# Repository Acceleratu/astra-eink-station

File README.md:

# A solar e-paper weather station

A build journal and prototype design by Acceleratu. Read the [English article](index.html) or the [Romanian article](ro.html). Both articles work directly from disk. The HTTP preview opens Markdown documents in the selected language. For the compact hardware download, open [station-project.zip](station-project.zip).

The design uses an nRF54L15 module, a 4.2-inch Waveshare e-paper panel, BME280, solar harvesting and USB-C charging. The hardware has been checked in software. Power-up, battery charging, radio range, USB plug fit and the fit of the printed enclosure still need to be tested on a prototype.

## Inside the project download

- Open `schematic/astra.sch`, `board/astra.brd` and `hardware/astra.lbr` as editable Autodesk Electronics / EAGLE sources. The PDF and assembly drawing are also included.
- `fab/` contains the manufacturing layers, drills, IPC netlist, BOM, placements, stencil geometry and test pad map. The catalog availability snapshot records the design date.
- `mechanical/` contains the populated board and assembled case in STEP, the enclosure generator, 11 printable STL files, drawings for the cut parts and the illustrated assembly guide. STEP preserves the assembly geometry. The CAD generator supplies editable dimensions and construction logic.
- `firmware/` contains the Zephyr source, host-side tests and the compiled Intel HEX. See its README for the pinned build environment.
- `docs/`, `verification/` and the project journal record engineering decisions, digital tests, exceptions and outstanding physical tests.

## Reading the evidence

The article uses the original test reports. SHA-256 values inside historical reports identify the files used for those runs. The distributed STEP headers, image/PDF metadata, drawing metadata, STL headers and Gerber export comments have been cleaned. STEP geometry and STL triangles are preserved. The USB inspection comparator uses the distributed assembly's checksum. Use the root `SHA256SUMS` to verify the download and the distributed files.

The archives contain the selected engineering deliverables. Third-party toolchains, vendor part libraries, cloud project archives, raw agent sessions and machine-specific build products are excluded. The usage table contains aggregate counts for the three hardware requests.

## Interactive explorer

Both articles include the same local viewer. Use it over HTTP. The seven schematic sheets have selectable reference designators and net labels. The PCB view combines the ten manufacturing plots with five CAD overlays. It includes a distance ruler in millimetres and component and net lookup. The 3D board includes 139 fitted components. The enclosure adds 111 named meshes and an exploded assembly, section cut and USB close-up. Rendered meshes are for inspection. The STEP assemblies and Gerber/drill exports remain the engineering files.

Open `?view=case&pose=spread#explorer` for the exploded assembly or `?view=pcb3&part=J101#explorer` for the USB connector. Use drag and pinch on touchscreens, or focus the viewport and use the arrow keys, +, − and 0. The viewer serves its own assets and Three.js. To rebuild the JavaScript, run `npm install` and `npm run build` in `explorer/`. The generator in `explorer/tools/drawings.py` takes the vector schematic PDF as its input. The public PDF is flattened. The mesh converter takes the original CAD presentation mesh manifest and the populated PCB STEP.

### Fusion workspace

The explorer opens with Fusion Electronics colours. All seven native schematic exports are registered to the interactive labels. Both standard PCB faces use the original Fusion exports. Custom layer combinations use the 37 individually exported design layers, registered on the board outline. The vector PDF and manufacturing plot views are available in the display selector.

The 3D canvas uses the saved Fusion orthographic cameras, the shaded assembly, a selectable orientation cube, grid, component browser and optional visible edges. The finished board uses meshes from the native 3D PCB, including the package bodies, plated holes, exposed lands and solder mask. Surface colours come from Fusion captures. Each projected sample is matched to the visible body and its depth. The component cameras cover the USB-C and FPC connectors, radio module, solar harvester, sensor and button. The original screenshots are available for direct comparison at full resolution. Their pixels are preserved losslessly. Browser rendering in freely chosen orientations uses WebGL.

Use `?workspace=1&view=case&camera=05-usb#explorer` to open the USB inspection camera in the full-window workspace. The local release contains all the data used by these views.

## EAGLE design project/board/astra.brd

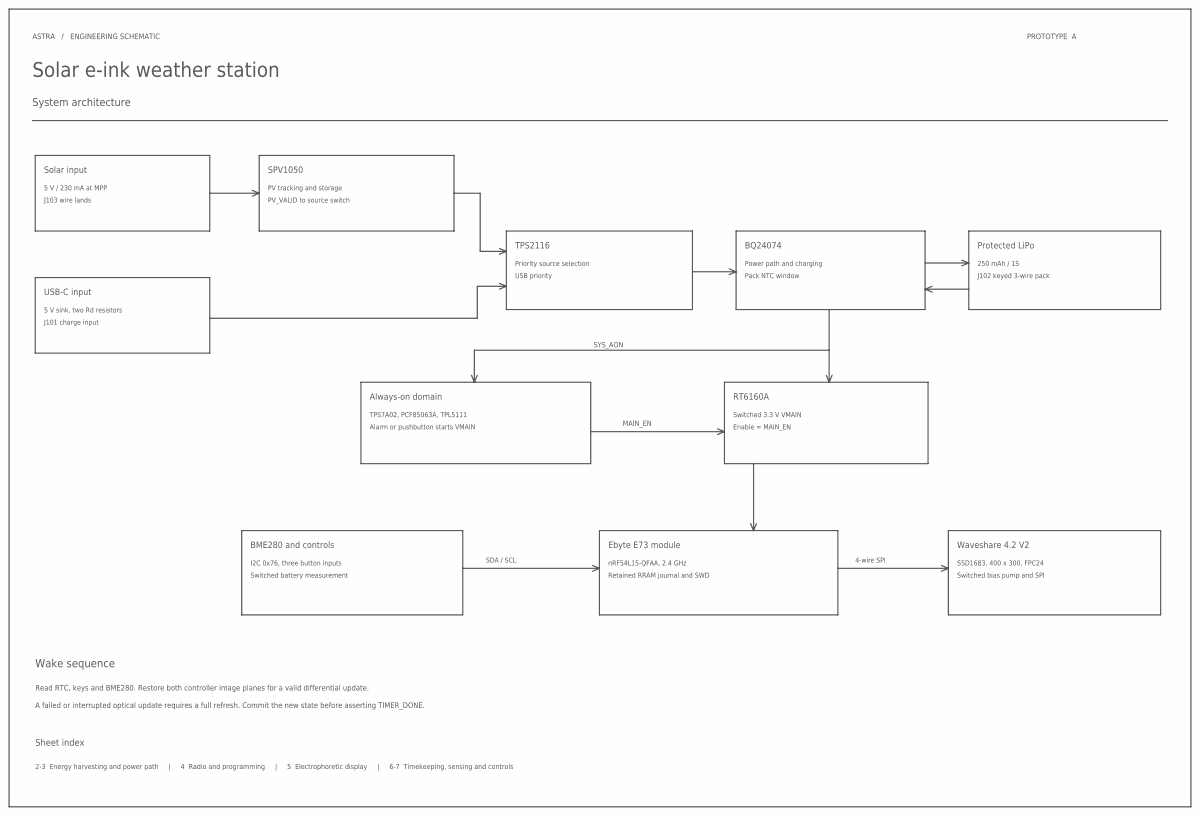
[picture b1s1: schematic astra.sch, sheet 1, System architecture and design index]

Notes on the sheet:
ASTRA / ENGINEERING SCHEMATIC
Solar e-ink weather station
System architecture
PROTOTYPE A
Solar input
5 V / 230 mA at MPP
J103 wire lands
USB-C input
5 V sink, two Rd resistors
J101 charge input
SPV1050
PV tracking and storage
PV_VALID to source switch
TPS2116
Priority source selection
USB priority
BQ24074
Power path and charging
Pack NTC window
Protected LiPo
250 mAh / 1S
J102 keyed 3-wire pack
RT6160A
Switched 3.3 V VMAIN
Enable = MAIN_EN
Always-on domain
TPS7A02, PCF85063A, TPL5111
Alarm or pushbutton starts VMAIN
SYS_AON
MAIN_EN
BME280 and controls
I2C 0x76, three button inputs
Switched battery measurement
Ebyte E73 module
nRF54L15-QFAA, 2.4 GHz
Retained RRAM journal and SWD
Waveshare 4.2 V2
SSD1683, 400 x 300, FPC24
Switched bias pump and SPI
SDA / SCL

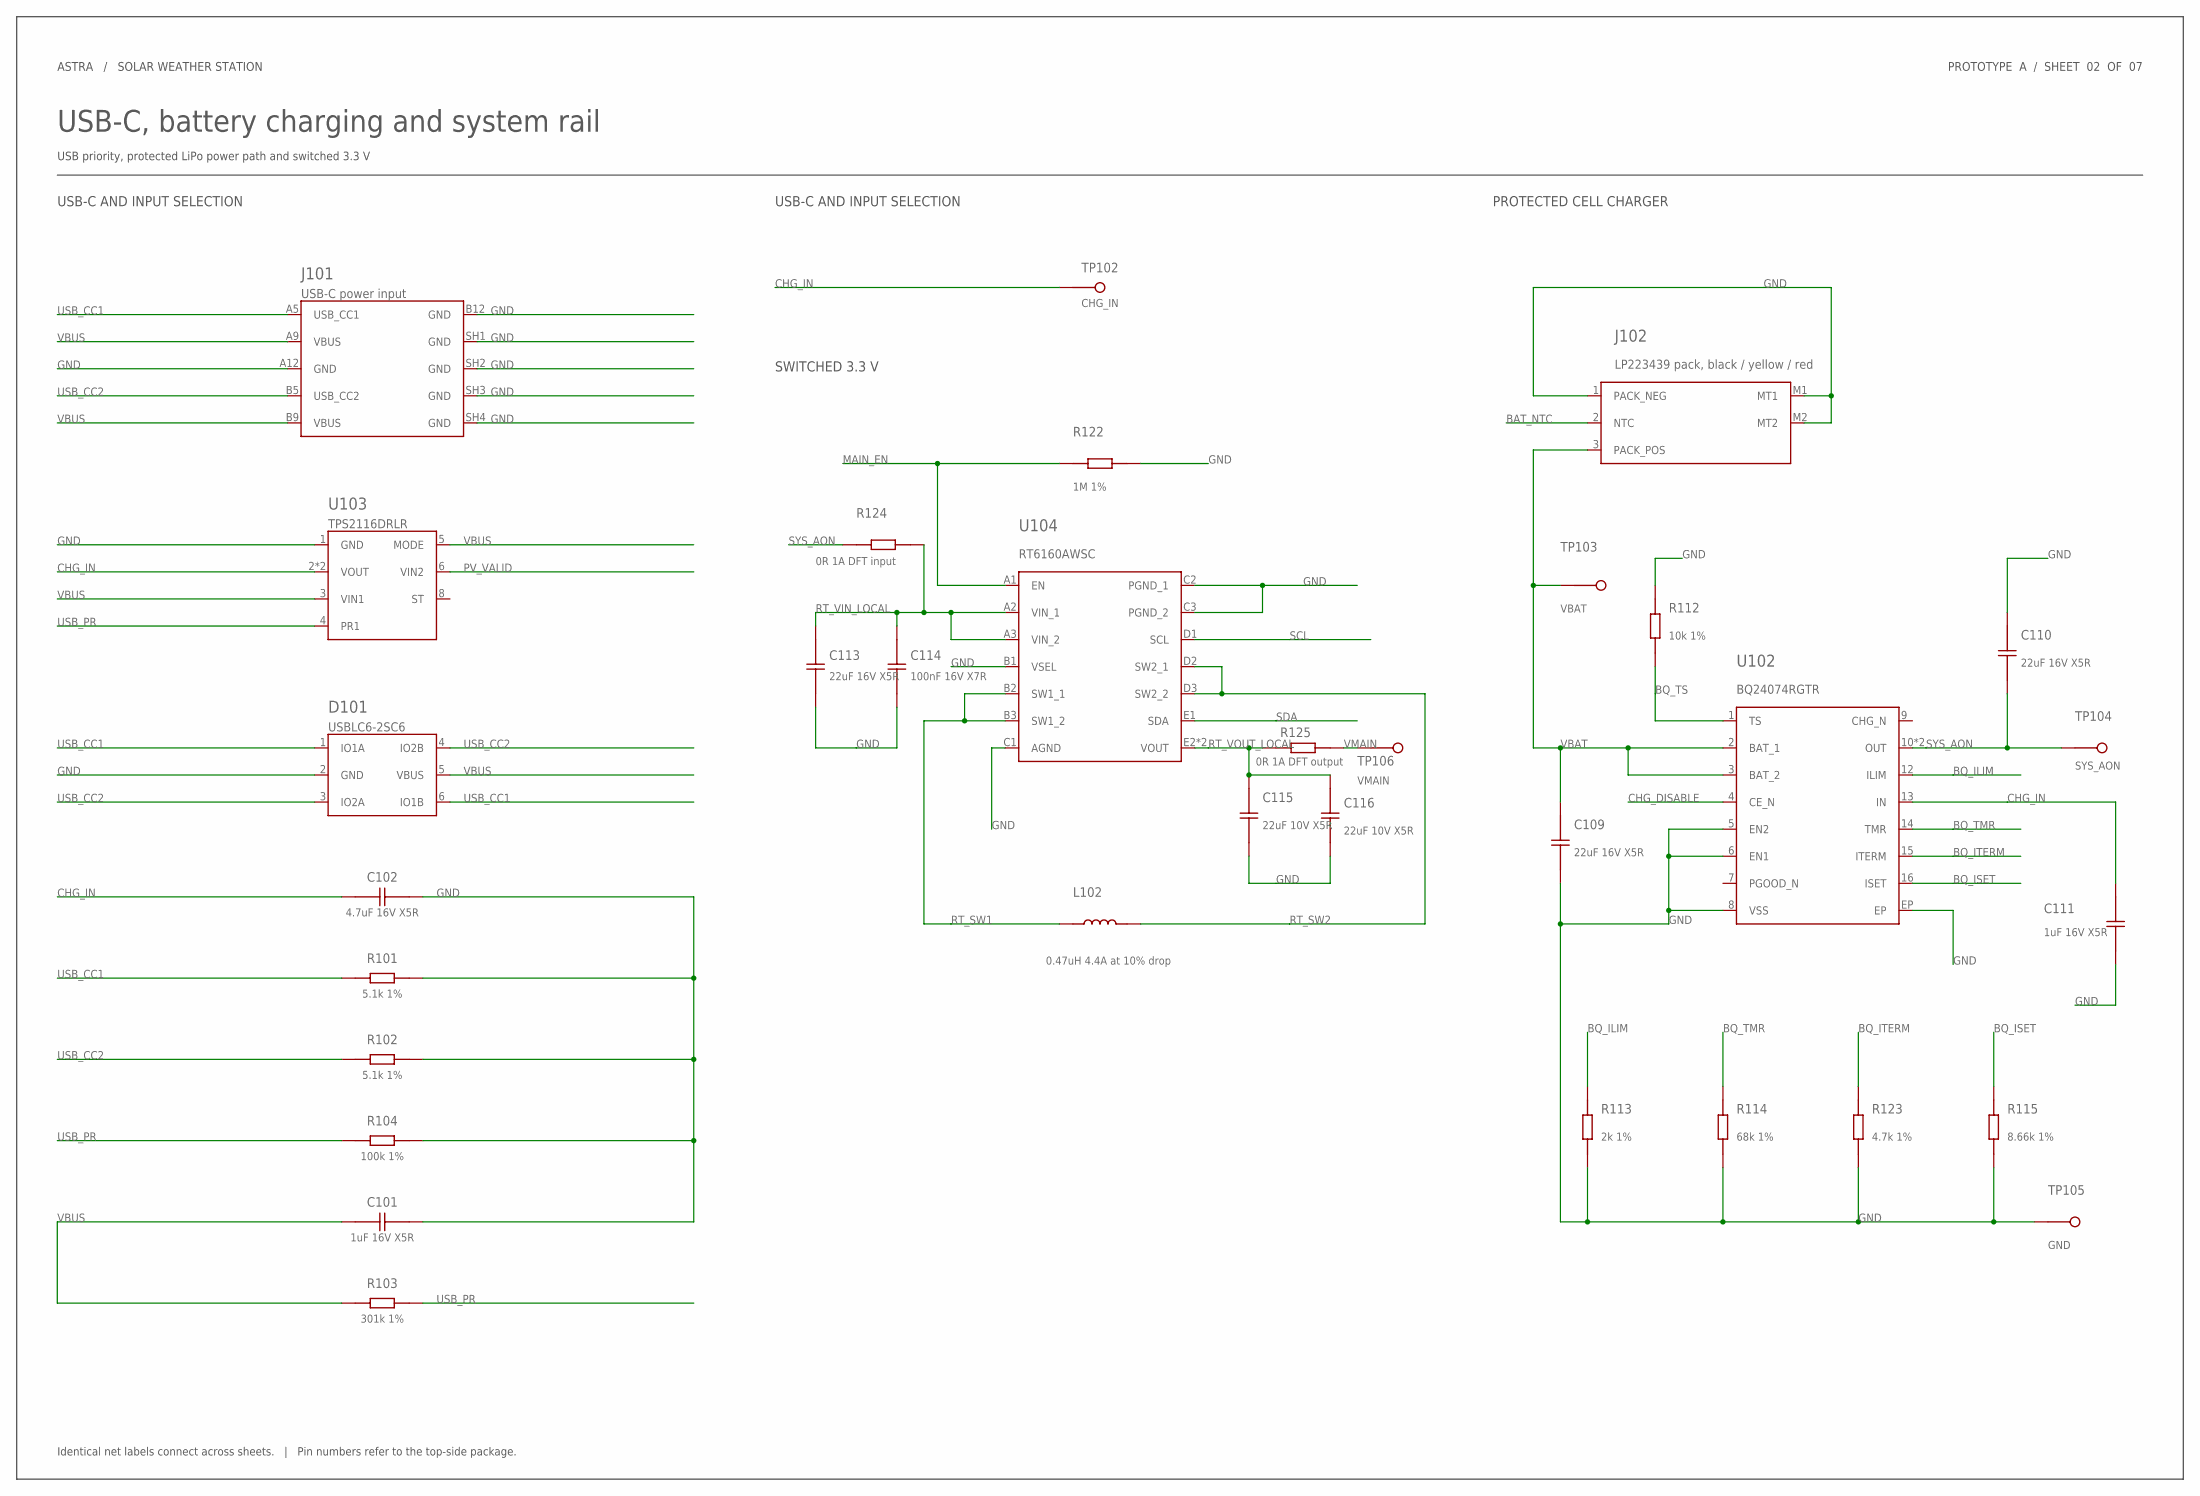
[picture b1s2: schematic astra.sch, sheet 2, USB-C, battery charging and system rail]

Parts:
C101, C111: 1uF 16V X5R; C0402; MPN CL05A105KO5NNNC; LCSC C29266
C102: 4.7uF 16V X5R; C0603; MPN GRM188R61C475KE11D; LCSC C77045
C109, C110, C113: 22uF 16V X5R; C0603; MPN GRM188R61C226ME01D; LCSC C5116073
C114: 100nF 16V X7R; C0402; MPN CL05B104KO5NNNC; LCSC C1525
C115, C116: 22uF 10V X5R; C0603; MPN GRM188R61A226ME15D; LCSC C84419
D101: USBLC6-2SC6; ST_SOT23_6_ESD; MPN USBLC6-2SC6; LCSC C7519
J101: USB-C power input; GCT_USB4135; MPN USB4135-GF-A; LCSC C5438410
J102: LP223439 pack, black / yellow / red; JST_ACH03P_POWER; MPN BM03B-ACHSS-GAN-ETF(LF)(SN); LCSC C5118705
L102: 0.47uH 4.4A at 10% drop; COIL_XGL4015; MPN XGL4015-471MEC; LCSC C5452431
R101, R102: 5.1k 1%; R0402; MPN 0402WGF5101TCE; LCSC C25905
R103: 301k 1%; R0402; MPN 0402WGF3013TCE; LCSC C25775
R104: 100k 1%; R0402; MPN 0402WGF1003TCE; LCSC C25741
R112: 10k 1%; R0402; MPN 0402WGF1002TCE; LCSC C25744
R113: 2k 1%; R0402; MPN 0402WGF2001TCE; LCSC C4109
R114: 68k 1%; R0402; MPN 0402WGF6802TCE; LCSC C36871
R115: 8.66k 1%; R0402; MPN 0402WGF8661TCE; LCSC C270576
R122: 1M 1%; R0402; MPN 0402WGF1004TCE; LCSC C26083
R123: 4.7k 1%; R0402; MPN 0402WGF4701TCE; LCSC C25900
R124: 0R 1A DFT input; R0603; MPN ERJ3GEY0R00V; LCSC C122704
R125: 0R 1A DFT output; R0603; MPN ERJ3GEY0R00V; LCSC C122704
TP102: CHG_IN; TP; MPN PCB-FEATURE
TP103: VBAT; TP; MPN PCB-FEATURE
TP104: SYS_AON; TP; MPN PCB-FEATURE
TP105: GND; TP; MPN PCB-FEATURE
TP106: VMAIN; TP; MPN PCB-FEATURE
U102: BQ24074RGTR; TI_RGT16_BQ74; MPN BQ24074RGTR; LCSC C54313
U103: TPS2116DRLR; TI_DRL8_MUX; MPN TPS2116DRLR; LCSC C3235557
U104: RT6160AWSC; RT_WLCSP15; MPN RT6160AWSC; LCSC C7065276

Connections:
BAT_NTC: J102.2 (NTC); also elsewhere on the board
BQ_ILIM: R113.1, U102.12 (ILIM)
BQ_ISET: R115.1, U102.16 (ISET)
BQ_ITERM: R123.1, U102.15 (ITERM)
BQ_TMR: R114.1, U102.14 (TMR)
BQ_TS: R112.1, U102.1 (TS)
CHG_DISABLE: U102.4 (CE_N); also elsewhere on the board
CHG_IN: C102.1, C111.1, TP102.1, U102.13 (IN), U103.2 (VOUT), U103.7 (VOUT); also elsewhere on the board
GND: C101.2, C102.2, C109.2, C110.2, C111.2, C113.2, C114.2, C115.2, C116.2, D101.2 (GND), J101.A12 (GND), J101.B12 (GND), J101.SH1 (GND), J101.SH2 (GND), J101.SH3 (GND), J101.SH4 (GND), J102.1 (PACK_NEG), J102.M1 (MT1), J102.M2 (MT2), R101.2, R102.2, R104.2, R112.2, R113.2, R114.2, R115.2, R122.2, R123.2, TP105.1, U102.5 (EN2), U102.6 (EN1), U102.8 (VSS), U102.EP, U103.1 (GND), U104.B1 (VSEL), U104.C1 (AGND), U104.C2 (PGND_1), U104.C3 (PGND_2); also elsewhere on the board
MAIN_EN: R122.1, U104.A1 (EN); also elsewhere on the board
PV_VALID: U103.6 (VIN2); also elsewhere on the board
RT_SW1: L102.1, U104.B2 (SW1_1), U104.B3 (SW1_2)
RT_SW2: L102.2, U104.D2 (SW2_1), U104.D3 (SW2_2)
RT_VIN_LOCAL: C113.1, C114.1, R124.1, U104.A2 (VIN_1), U104.A3 (VIN_2)
RT_VOUT_LOCAL: C115.1, C116.1, R125.1, U104.E2 (VOUT), U104.E3 (VOUT)
SCL: U104.D1 (SCL); also elsewhere on the board
SDA: U104.E1 (SDA); also elsewhere on the board
SYS_AON: C110.1, R124.2, TP104.1, U102.10 (OUT), U102.11 (OUT); also elsewhere on the board
USB_CC1: D101.1 (IO1A), D101.6 (IO1B), J101.A5 (USB_CC1), R101.1
USB_CC2: D101.3 (IO2A), D101.4 (IO2B), J101.B5 (USB_CC2), R102.1
USB_PR: R103.2, R104.1, U103.4 (PR1)
VBAT: C109.1, J102.3 (PACK_POS), TP103.1, U102.2 (BAT_1), U102.3 (BAT_2); also elsewhere on the board
VBUS: C101.1, D101.5 (VBUS), J101.A9 (VBUS), J101.B9 (VBUS), R103.1, U103.3 (VIN1), U103.5 (MODE)
VMAIN: R125.2, TP106.1; also elsewhere on the board

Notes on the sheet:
ASTRA / SOLAR WEATHER STATION
USB-C, battery charging and system rail
USB priority, protected LiPo power path and switched 3.3 V
PROTOTYPE A / SHEET 02 OF 07
Identical net labels connect across sheets. | Pin numbers refer to the top-side package.
USB-C AND INPUT SELECTION
PROTECTED CELL CHARGER
SWITCHED 3.3 V

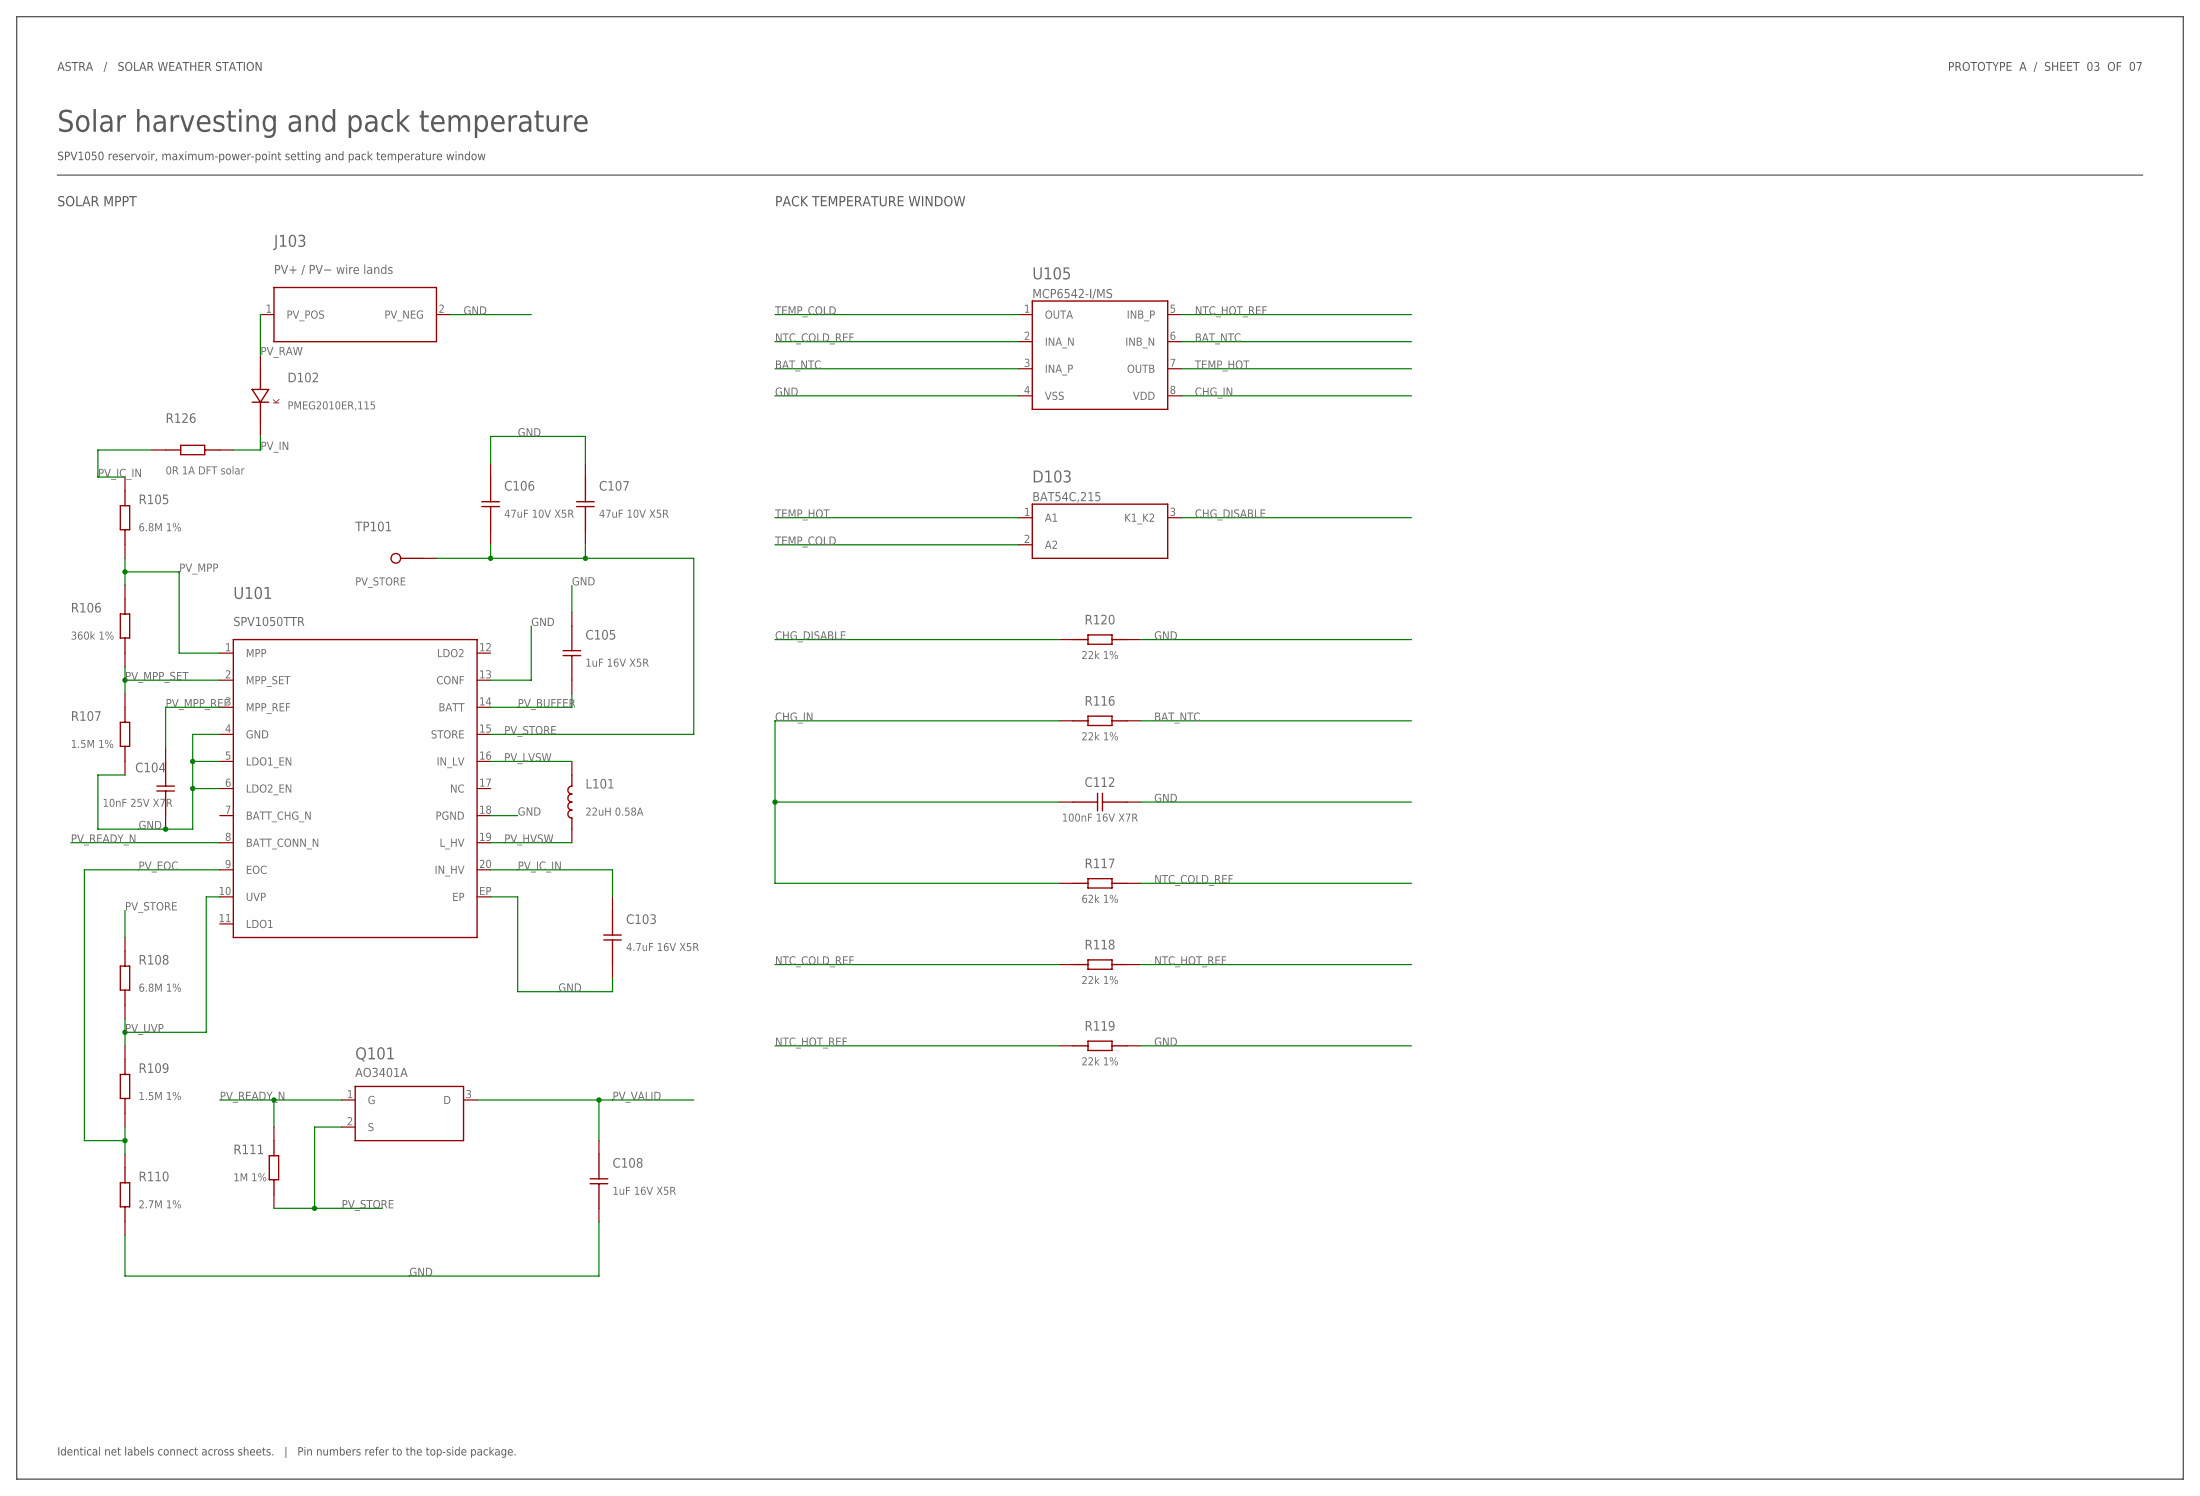
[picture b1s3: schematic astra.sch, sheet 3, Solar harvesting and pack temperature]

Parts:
C103: 4.7uF 16V X5R; C0603; MPN GRM188R61C475KE11D; LCSC C77045
C104: 10nF 25V X7R; C0402; MPN CL05B103KA5NNNC; LCSC C318576
C105, C108: 1uF 16V X5R; C0402; MPN CL05A105KO5NNNC; LCSC C29266
C106, C107: 47uF 10V X5R; C1206P; MPN GRM31CR61A476KE15L; LCSC C426659
C112: 100nF 16V X7R; C0402; MPN CL05B104KO5NNNC; LCSC C1525
D102: PMEG2010ER,115; NXP_CFP3_DIODE; MPN PMEG2010ER,115; LCSC C82288
D103: BAT54C,215; NXP_SOT23_DIODE; MPN BAT54C,215; LCSC C37704
J103: PV+ / PV− wire lands; PV_WIRE_PAIR; MPN PCB-FEATURE
L101: 22uH 0.58A; BOURNS_SRN3015; MPN SRN3015-220M; LCSC C2918094
Q101: AO3401A; SOT23_AO3401A; MPN AO3401A; LCSC C15127
R105, R108: 6.8M 1%; R0402; MPN 0402WGF6804TCE; LCSC C620473
R106: 360k 1%; R0402; MPN 0402WGF3603TCE; LCSC C45956
R107, R109: 1.5M 1%; R0402; MPN 0402WGF1504TCE; LCSC C22276
R110: 2.7M 1%; R0402; MPN 0402WGF2704TCE; LCSC C270621
R111: 1M 1%; R0402; MPN 0402WGF1004TCE; LCSC C26083
R116, R118, R119, R120: 22k 1%; R0402; MPN 0402WGF2202TCE; LCSC C25768
R117: 62k 1%; R0402; MPN 0402WGF6202TCE; LCSC C37825
R126: 0R 1A DFT solar; R0603; MPN ERJ3GEY0R00V; LCSC C122704
TP101: PV_STORE; TP; MPN PCB-FEATURE
U101: SPV1050TTR; SPV_VFQFPN20; MPN SPV1050TTR; LCSC C5181469
U105: MCP6542-I/MS; MC_MSOP8_TEMP; MPN MCP6542-I/MS; LCSC C636338

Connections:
BAT_NTC: R116.2, U105.3 (INA_P), U105.6 (INB_N); also elsewhere on the board
CHG_DISABLE: D103.3 (K1_K2), R120.1; also elsewhere on the board
CHG_IN: C112.1, R116.1, R117.1, U105.8 (VDD); also elsewhere on the board
GND: C103.2, C104.2, C105.2, C106.2, C107.2, C108.2, C112.2, J103.2 (PV_NEG), R107.2, R110.2, R119.2, R120.2, U101.4 (GND), U101.5 (LDO1_EN), U101.6 (LDO2_EN), U101.13 (CONF), U101.18 (PGND), U101.EP, U105.4 (VSS); also elsewhere on the board
NTC_COLD_REF: R117.2, R118.1, U105.2 (INA_N)
NTC_HOT_REF: R118.2, R119.1, U105.5 (INB_P)
PV_BUFFER: C105.1, U101.14 (BATT)
PV_EOC: R109.2, R110.1, U101.9 (EOC)
PV_HVSW: L101.1, U101.19 (L_HV)
PV_IC_IN: C103.1, R105.1, R126.1, U101.20 (IN_HV)
PV_IN: D102.1 (K), R126.2
PV_LVSW: L101.2, U101.16 (IN_LV)
PV_MPP: R105.2, R106.1, U101.1 (MPP)
PV_MPP_REF: C104.1, U101.3 (MPP_REF)
PV_MPP_SET: R106.2, R107.1, U101.2 (MPP_SET)
PV_RAW: D102.2 (A), J103.1 (PV_POS)
PV_READY_N: Q101.1 (G), R111.1, U101.8 (BATT_CONN_N)
PV_STORE: C106.1, C107.1, Q101.2 (S), R108.1, R111.2, TP101.1, U101.15 (STORE)
PV_UVP: R108.2, R109.1, U101.10 (UVP)
PV_VALID: C108.1, Q101.3 (D); also elsewhere on the board
TEMP_COLD: D103.2 (A2), U105.1 (OUTA)
TEMP_HOT: D103.1 (A1), U105.7 (OUTB)

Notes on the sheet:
ASTRA / SOLAR WEATHER STATION
Solar harvesting and pack temperature
SPV1050 reservoir, maximum-power-point setting and pack temperature window
PROTOTYPE A / SHEET 03 OF 07
Identical net labels connect across sheets. | Pin numbers refer to the top-side package.
SOLAR MPPT
PACK TEMPERATURE WINDOW

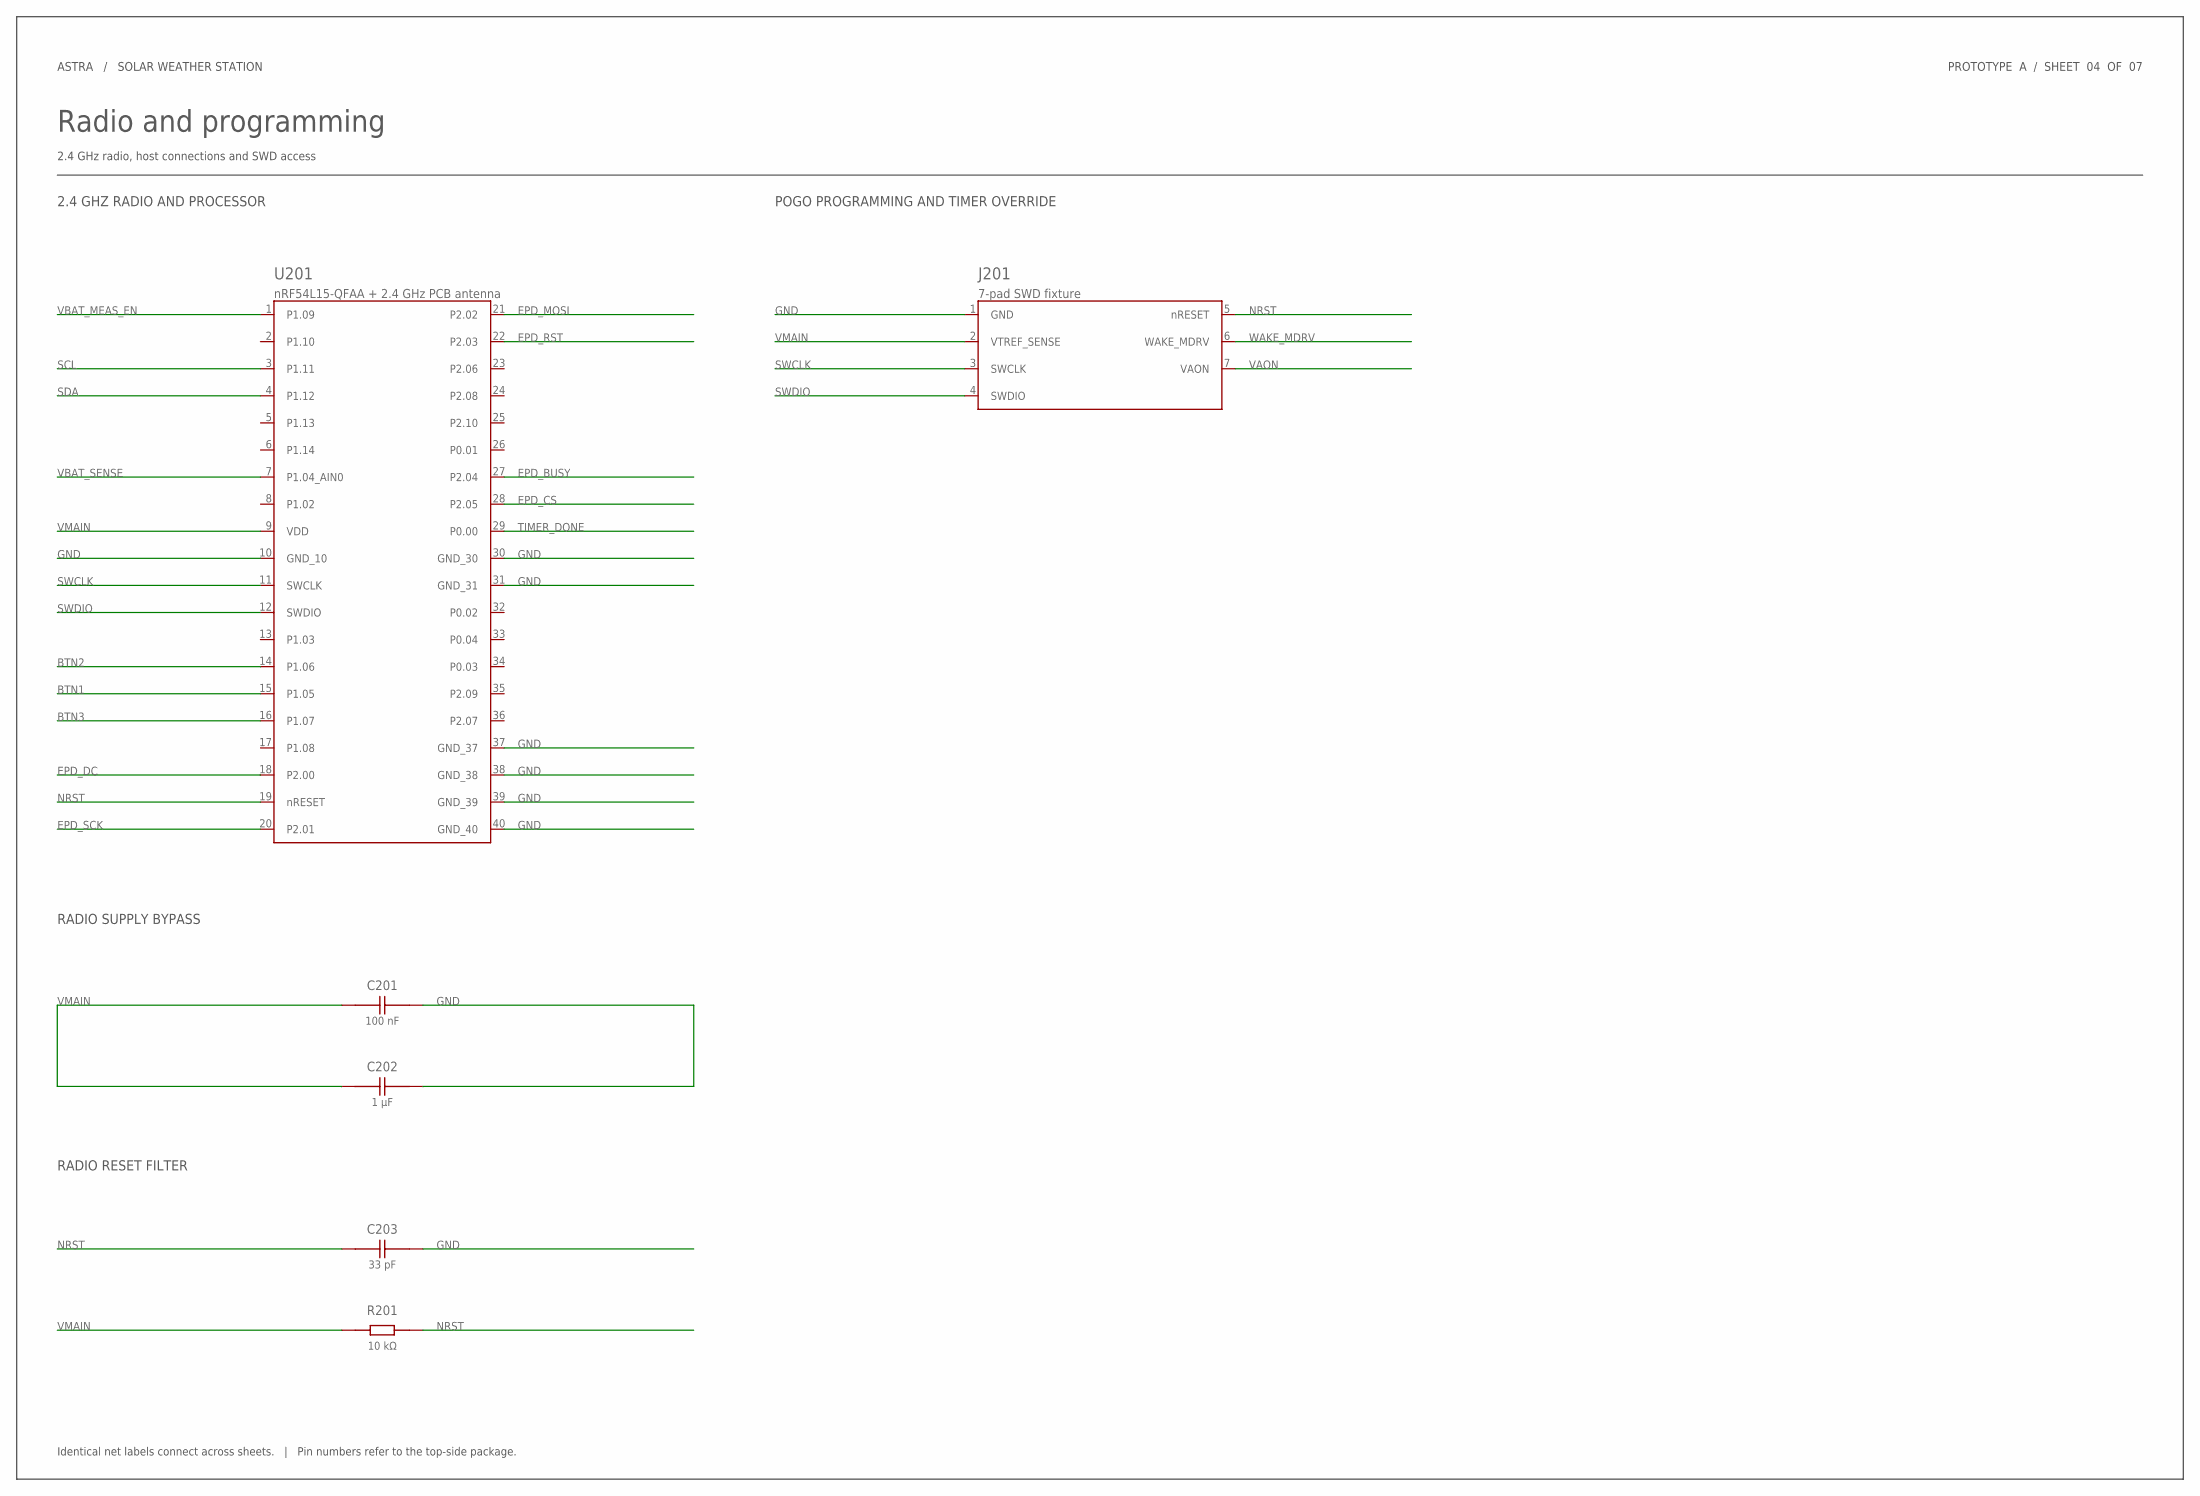
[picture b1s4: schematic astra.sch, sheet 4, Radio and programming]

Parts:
C201: 100 nF; C0402; MPN CL05B104KO5NNNC; LCSC C1525
C202: 1 µF; C0402; MPN CL05A105KA5NQNC; LCSC C52923
C203: 33 pF; C0402; MPN 0402CG330J500NT; LCSC C1562
J201: 7-pad SWD fixture; SWD_FIXTURE_7; MPN PCB pads only
R201: 10 kΩ; R0402; MPN 0402WGF1002TCE; LCSC C25744
U201: nRF54L15-QFAA + 2.4 GHz PCB antenna; EBYTE_08S1F_LGA40; MPN E73-2G4M08S1F; LCSC C54337734

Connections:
BTN1: U201.15 (P1.05); also elsewhere on the board
BTN2: U201.14 (P1.06); also elsewhere on the board
BTN3: U201.16 (P1.07); also elsewhere on the board
EPD_BUSY: U201.27 (P2.04); also elsewhere on the board
EPD_CS: U201.28 (P2.05); also elsewhere on the board
EPD_DC: U201.18 (P2.00); also elsewhere on the board
EPD_MOSI: U201.21 (P2.02); also elsewhere on the board
EPD_RST: U201.22 (P2.03); also elsewhere on the board
EPD_SCK: U201.20 (P2.01); also elsewhere on the board
GND: C201.2, C202.2, C203.2, J201.1 (GND), U201.10 (GND_10), U201.30 (GND_30), U201.31 (GND_31), U201.37 (GND_37), U201.38 (GND_38), U201.39 (GND_39), U201.40 (GND_40); also elsewhere on the board
NRST: C203.1, J201.5 (nRESET), R201.2, U201.19 (nRESET)
SCL: U201.3 (P1.11); also elsewhere on the board
SDA: U201.4 (P1.12); also elsewhere on the board
SWCLK: J201.3 (SWCLK), U201.11 (SWCLK)
SWDIO: J201.4 (SWDIO), U201.12 (SWDIO)
TIMER_DONE: U201.29 (P0.00); also elsewhere on the board
VAON: J201.7 (VAON); also elsewhere on the board
VBAT_MEAS_EN: U201.1 (P1.09); also elsewhere on the board
VBAT_SENSE: U201.7 (P1.04_AIN0); also elsewhere on the board
VMAIN: C201.1, C202.1, J201.2 (VTREF_SENSE), R201.1, U201.9 (VDD); also elsewhere on the board
WAKE_MDRV: J201.6 (WAKE_MDRV); also elsewhere on the board

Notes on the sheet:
ASTRA / SOLAR WEATHER STATION
Radio and programming
2.4 GHz radio, host connections and SWD access
PROTOTYPE A / SHEET 04 OF 07
Identical net labels connect across sheets. | Pin numbers refer to the top-side package.
2.4 GHZ RADIO AND PROCESSOR
RADIO SUPPLY BYPASS
RADIO RESET FILTER
POGO PROGRAMMING AND TIMER OVERRIDE

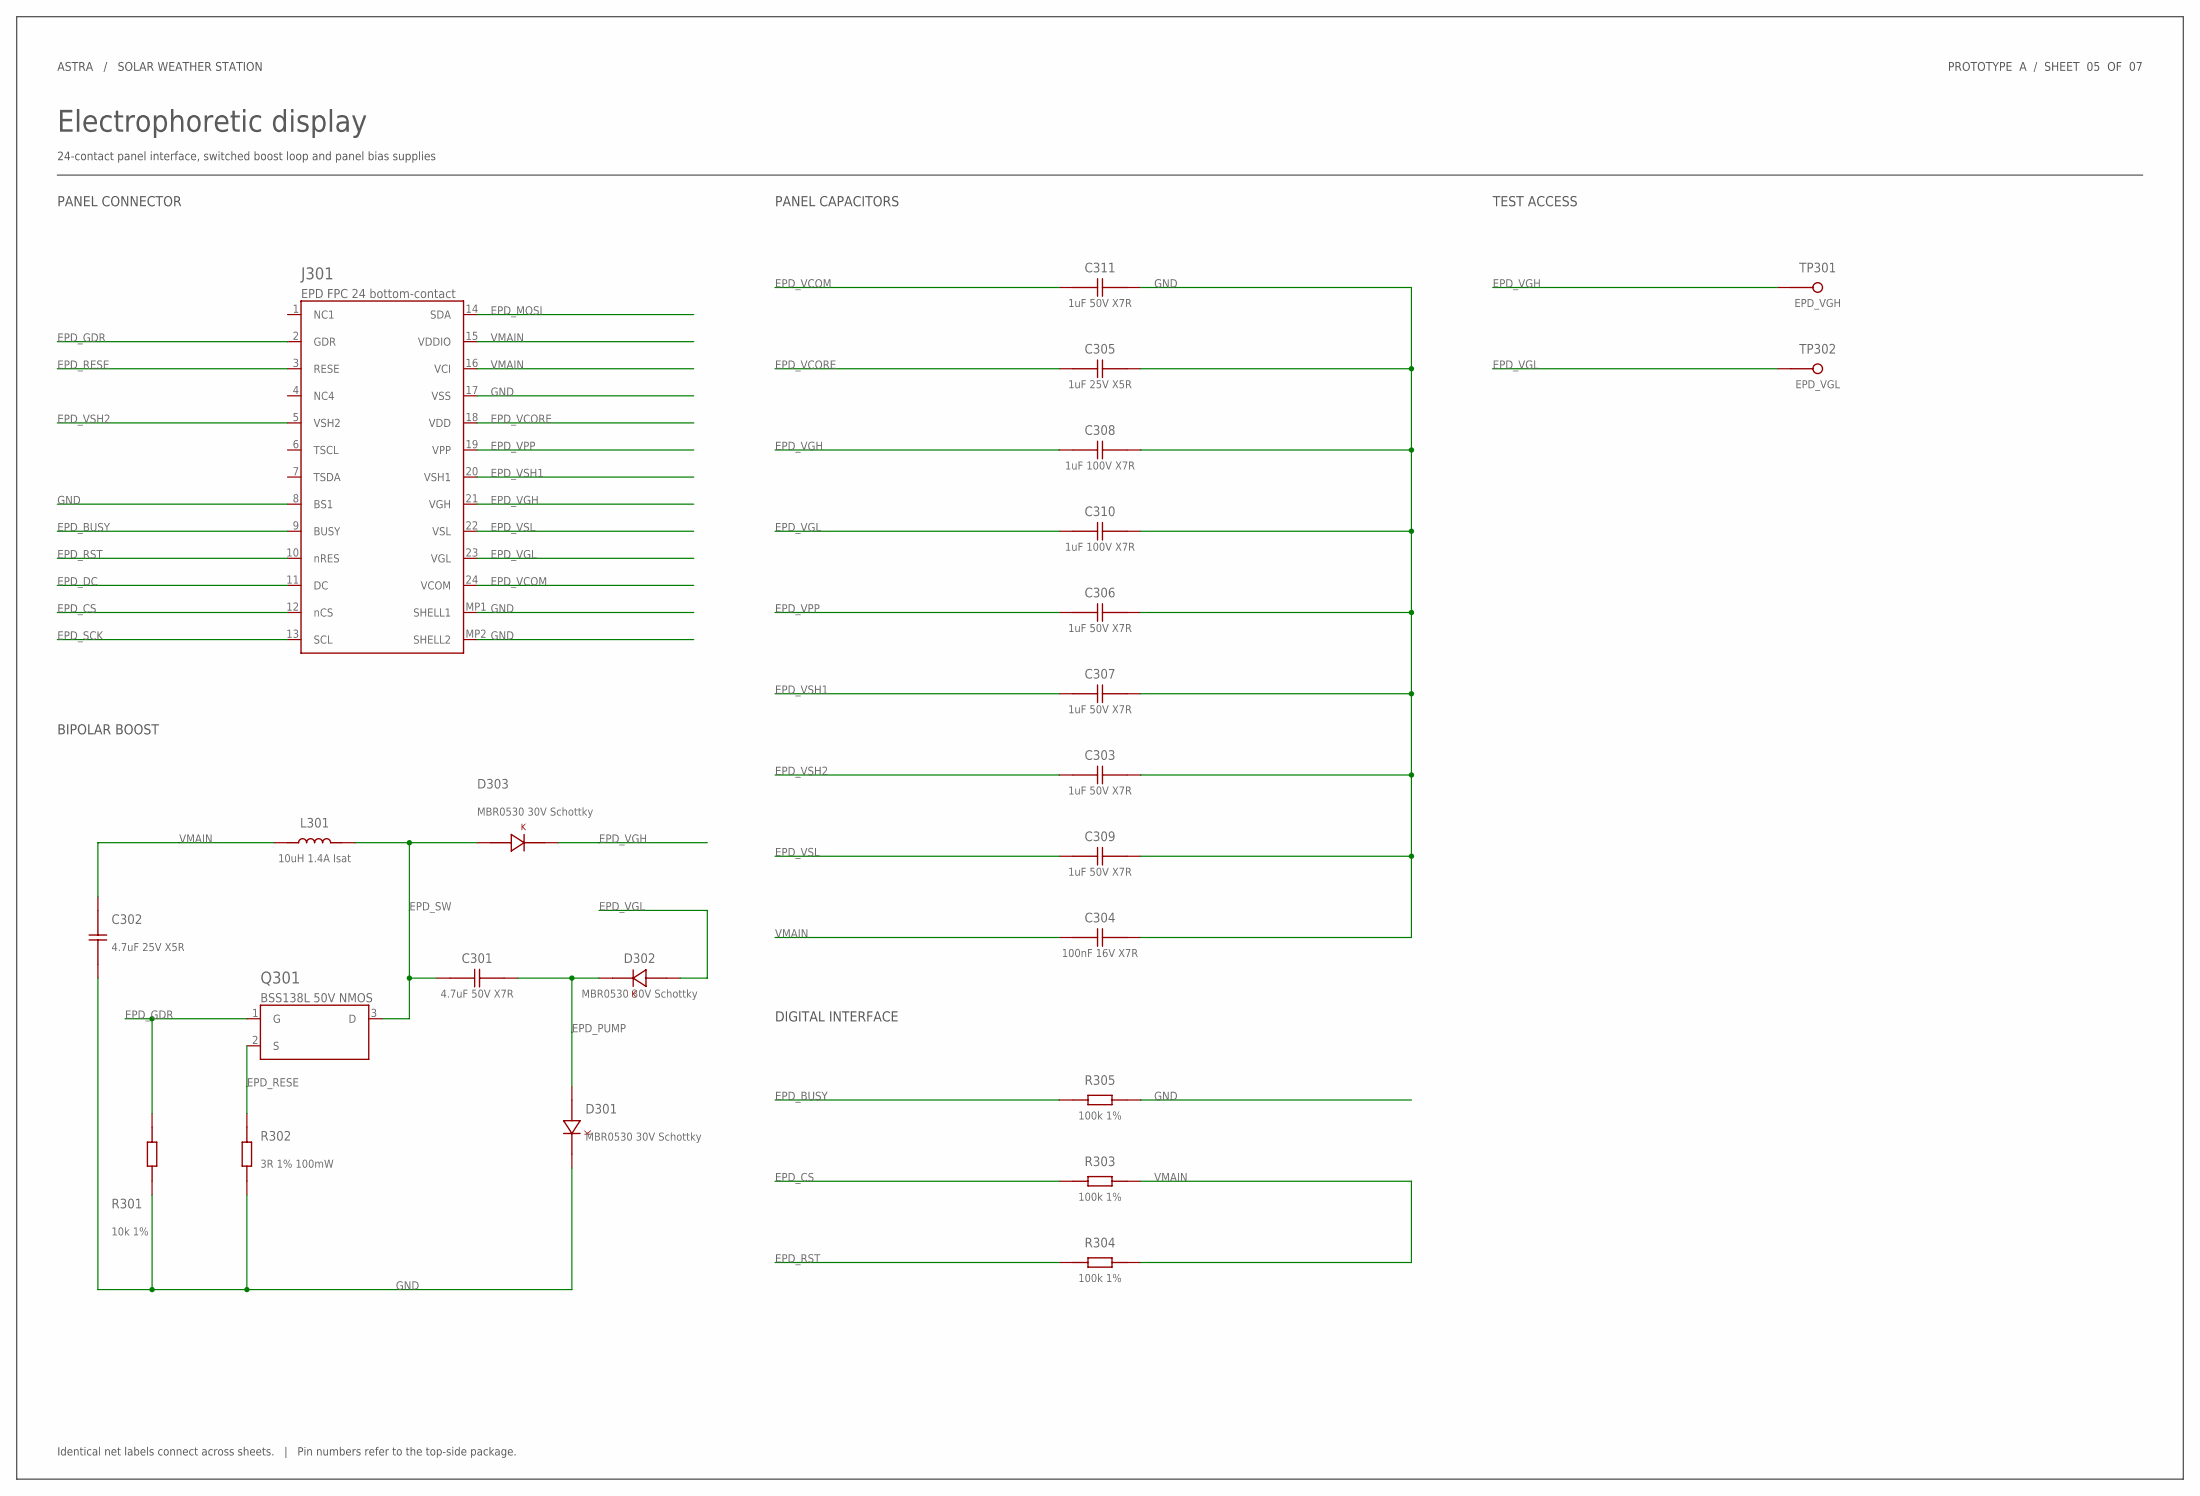
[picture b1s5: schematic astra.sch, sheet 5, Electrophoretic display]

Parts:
C301: 4.7uF 50V X7R; EPD_C1210; MPN CL32B475KBJNNNE; LCSC C47783
C302: 4.7uF 25V X5R; C0805; MPN CL21A475KAQNNNE; LCSC C1779
C303, C306, C307, C309, C311: 1uF 50V X7R; C0805; MPN CL21B105KBFNNNE; LCSC C28323
C304: 100nF 16V X7R; C0402; MPN CL05B104KO5NNNC; LCSC C1525
C305: 1uF 25V X5R; C0402; MPN CL05A105KA5NQNC; LCSC C52923
C308, C310: 1uF 100V X7R; EPD_C1206; MPN CL31B105KCHNNNE; LCSC C13832
D301, D302, D303: MBR0530 30V Schottky; MBR0530_CASE425; MPN MBR0530T1G; LCSC C82046
J301: EPD FPC 24 bottom-contact; FH12_24S_05SH; MPN FH12-24S-0.5SH(55); LCSC C202112
L301: 10uH 1.4A Isat; SRN4018; MPN SRN4018-100M; LCSC C503307
Q301: BSS138L 50V NMOS; BSS138_CASE318; MPN BSS138LT1G; LCSC C82045
R301: 10k 1%; R0402; MPN 0402WGF1002TCE; LCSC C25744
R302: 3R 1% 100mW; R0603; MPN RC0603FR-073RL; LCSC C137724
R303, R304, R305: 100k 1%; R0402; MPN 0402WGF1003TCE; LCSC C25741
TP301: EPD_VGH; TP; MPN PCB test land
TP302: EPD_VGL; TP; MPN PCB test land

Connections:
EPD_BUSY: J301.9 (BUSY), R305.1; also elsewhere on the board
EPD_CS: J301.12 (nCS), R303.1; also elsewhere on the board
EPD_DC: J301.11 (DC); also elsewhere on the board
EPD_GDR: J301.2 (GDR), Q301.1 (G), R301.2
EPD_MOSI: J301.14 (SDA); also elsewhere on the board
EPD_PUMP: C301.2, D301.2 (A), D302.1 (K)
EPD_RESE: J301.3 (RESE), Q301.2 (S), R302.2
EPD_RST: J301.10 (nRES), R304.1; also elsewhere on the board
EPD_SCK: J301.13 (SCL); also elsewhere on the board
EPD_SW: C301.1, D303.2 (A), L301.2, Q301.3 (D)
EPD_VCOM: C311.1, J301.24 (VCOM)
EPD_VCORE: C305.1, J301.18 (VDD)
EPD_VGH: C308.1, D303.1 (K), J301.21 (VGH), TP301.1
EPD_VGL: C310.1, D302.2 (A), J301.23 (VGL), TP302.1
EPD_VPP: C306.1, J301.19 (VPP)
EPD_VSH1: C307.1, J301.20 (VSH1)
EPD_VSH2: C303.1, J301.5 (VSH2)
EPD_VSL: C309.1, J301.22 (VSL)
GND: C302.2, C303.2, C304.2, C305.2, C306.2, C307.2, C308.2, C309.2, C310.2, C311.2, D301.1 (K), J301.8 (BS1), J301.17 (VSS), J301.MP1 (SHELL1), J301.MP2 (SHELL2), R301.1, R302.1, R305.2; also elsewhere on the board
VMAIN: C302.1, C304.1, J301.15 (VDDIO), J301.16 (VCI), L301.1, R303.2, R304.2; also elsewhere on the board

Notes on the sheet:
ASTRA / SOLAR WEATHER STATION
Electrophoretic display
24-contact panel interface, switched boost loop and panel bias supplies
PROTOTYPE A / SHEET 05 OF 07
Identical net labels connect across sheets. | Pin numbers refer to the top-side package.
PANEL CONNECTOR
BIPOLAR BOOST
PANEL CAPACITORS
DIGITAL INTERFACE
TEST ACCESS
